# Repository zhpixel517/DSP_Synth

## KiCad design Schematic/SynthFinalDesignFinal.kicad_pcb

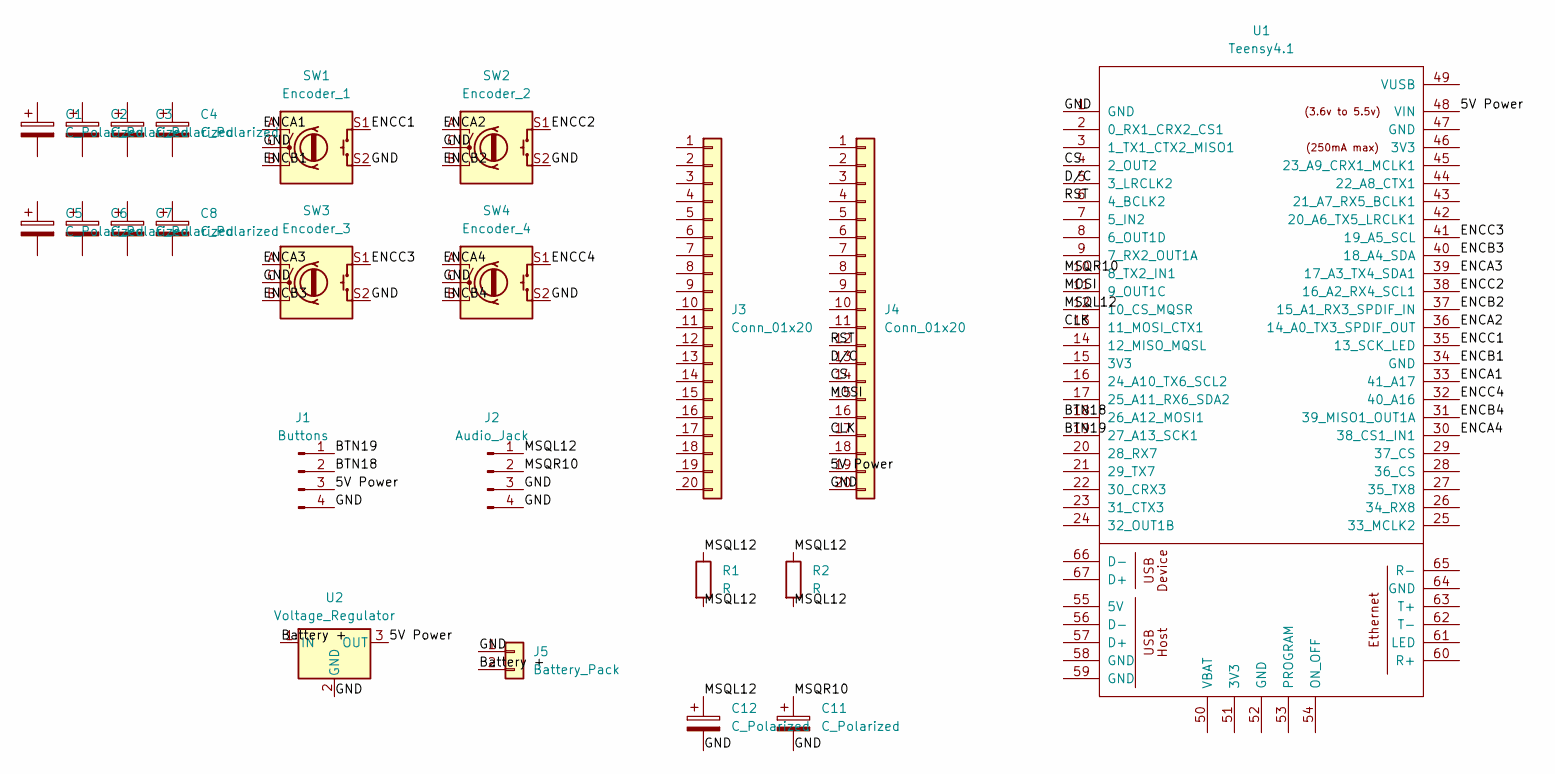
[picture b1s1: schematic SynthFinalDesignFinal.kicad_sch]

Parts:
C1, C2, C3, C4, C5, C6, C7, C8, C11, C12: C_Polarized; CP_Radial_D5.0mm_P2.00mm
J1: Buttons; PinHeader_1x04_P2.54mm_Vertical
J2: Audio_Jack; PinHeader_1x04_P2.54mm_Vertical
J3, J4: Conn_01x20; PinHeader_1x20_P2.54mm_Vertical
J5: Battery_Pack; PinHeader_1x02_P2.54mm_Vertical
R1, R2: R; R_Axial_DIN0207_L6.3mm_D2.5mm_P7.62mm_Horizontal
SW1: Encoder_1; RotaryEncoder_Alps_EC11E-Switch_Vertical_H20mm
SW2: Encoder_2; RotaryEncoder_Alps_EC11E-Switch_Vertical_H20mm
SW3: Encoder_3; RotaryEncoder_Alps_EC11E-Switch_Vertical_H20mm
SW4: Encoder_4; RotaryEncoder_Alps_EC11E-Switch_Vertical_H20mm
U1: Teensy4.1; Teensy41
U2: Voltage_Regulator; TO-220-3_Vertical

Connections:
/5V Power: J1.3, J4.19, U1.48 (VIN), U2.3 (OUT)
/BTN18: J1.2, U1.18 (26_A12_MOSI1)
/BTN19: J1.1, U1.19 (27_A13_SCK1)
/Battery +: J5.2, U2.1 (IN)
/CLK: J4.17, U1.13 (11_MOSI_CTX1)
/CS: J4.14, U1.4 (2_OUT2)
/D/C: J4.13, U1.5 (3_LRCLK2)
/ENCA1: SW1.A, U1.33 (41_A17)
/ENCA2: SW2.A, U1.36 (14_A0_TX3_SPDIF_OUT)
/ENCA3: SW3.A, U1.39 (17_A3_TX4_SDA1)
/ENCA4: SW4.A, U1.30 (38_CS1_IN1)
/ENCB1: SW1.B, U1.34 (GND)
/ENCB2: SW2.B, U1.37 (15_A1_RX3_SPDIF_IN)
/ENCB3: SW3.B, U1.40 (18_A4_SDA)
/ENCB4: SW4.B, U1.31 (39_MISO1_OUT1A)
/ENCC1: SW1.S1, U1.35 (13_SCK_LED)
/ENCC2: SW2.S1, U1.38 (16_A2_RX4_SCL1)
/ENCC3: SW3.S1, U1.41 (19_A5_SCL)
/ENCC4: SW4.S1, U1.32 (40_A16)
/GND: C11.2, C12.2, J1.4, J2.3, J2.4, J4.20, J5.1, SW1.C, SW1.S2, SW2.C, SW2.S2, SW3.C, SW3.S2, SW4.C, SW4.S2, U1.1 (GND), U2.2 (GND)
/MOSI: J4.15, U1.11 (9_OUT1C)
/MSQL12: C12.1, J2.1, R1.1, R1.2, R2.1, R2.2, U1.12 (10_CS_MQSR)
/MSQR10: C11.1, J2.2, U1.10 (8_TX2_IN1)
/RST: J4.12, U1.6 (4_BCLK2)

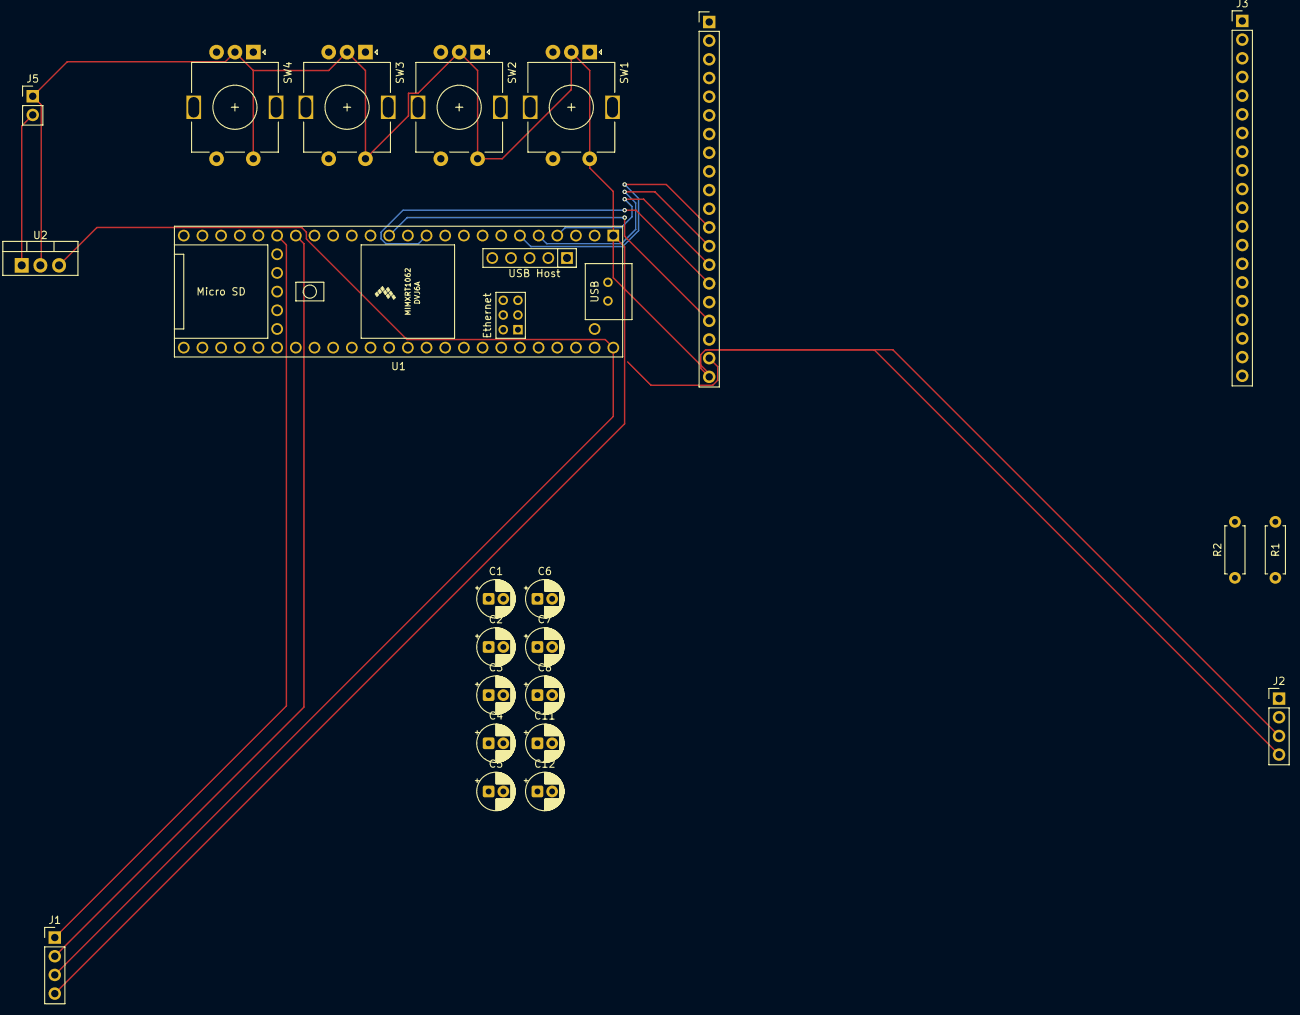
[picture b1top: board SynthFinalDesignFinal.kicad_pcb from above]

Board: 2 copper layers, 23 parts (0 on the bottom side), 24 nets.
